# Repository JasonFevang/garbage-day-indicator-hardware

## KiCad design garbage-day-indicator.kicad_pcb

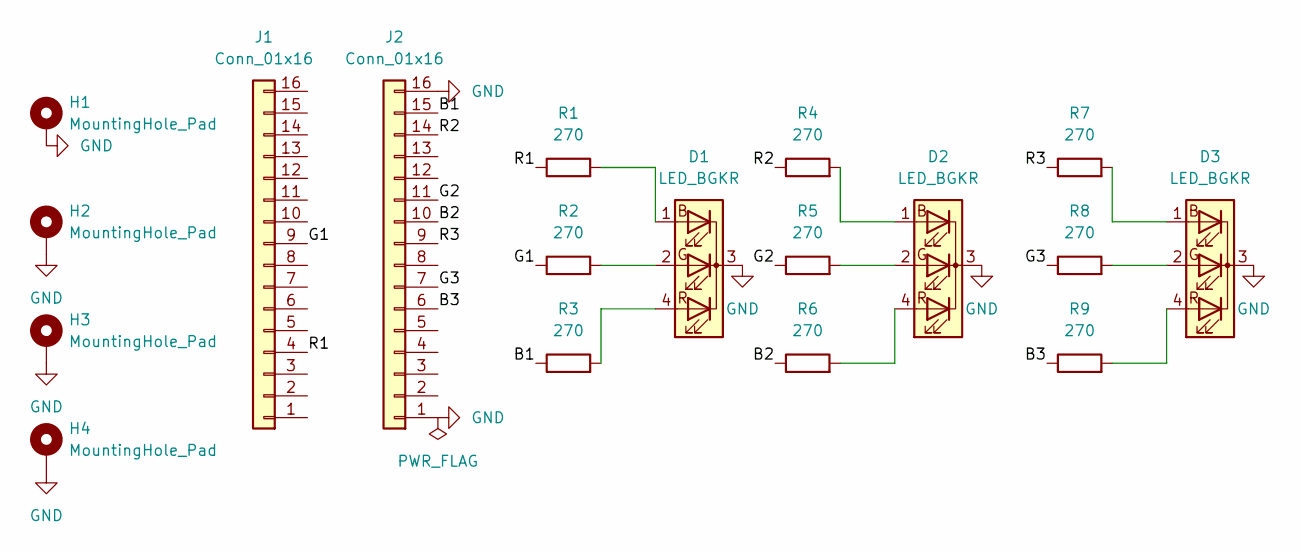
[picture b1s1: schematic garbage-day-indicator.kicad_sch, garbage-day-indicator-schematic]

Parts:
D1, D2, D3: LED_BGKR; LED_D5.0mm-4_RGB
H1, H2, H3, H4: MountingHole_Pad; MountingHole_3.2mm_M3_DIN965_Pad
J1, J2: Conn_01x16; PinSocket_1x16_P2.54mm_Vertical
R1, R2, R3, R4, R5, R6, R7, R8, R9: 270; R_0603_1608Metric

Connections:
/B1: J2.15, R3.1
/B2: J2.10, R6.1
/B3: J2.6, R9.1
/G1: J1.9, R2.1
/G2: J2.11, R5.1
/G3: J2.7, R8.1
/R1: J1.4, R1.1
/R2: J2.14, R4.1
/R3: J2.9, R7.1
GND: D1.3 (K), D2.3 (K), D3.3 (K), H1.1, H2.1, H3.1, H4.1, J2.1, J2.16
unnamed: D1.1 (BA), R1.2
unnamed: D1.2 (GA), R2.2
unnamed: D1.4 (RA), R3.2
unnamed: D2.1 (BA), R4.2
unnamed: D2.2 (GA), R5.2
unnamed: D2.4 (RA), R6.2
unnamed: D3.1 (BA), R7.2
unnamed: D3.2 (GA), R8.2
unnamed: D3.4 (RA), R9.2

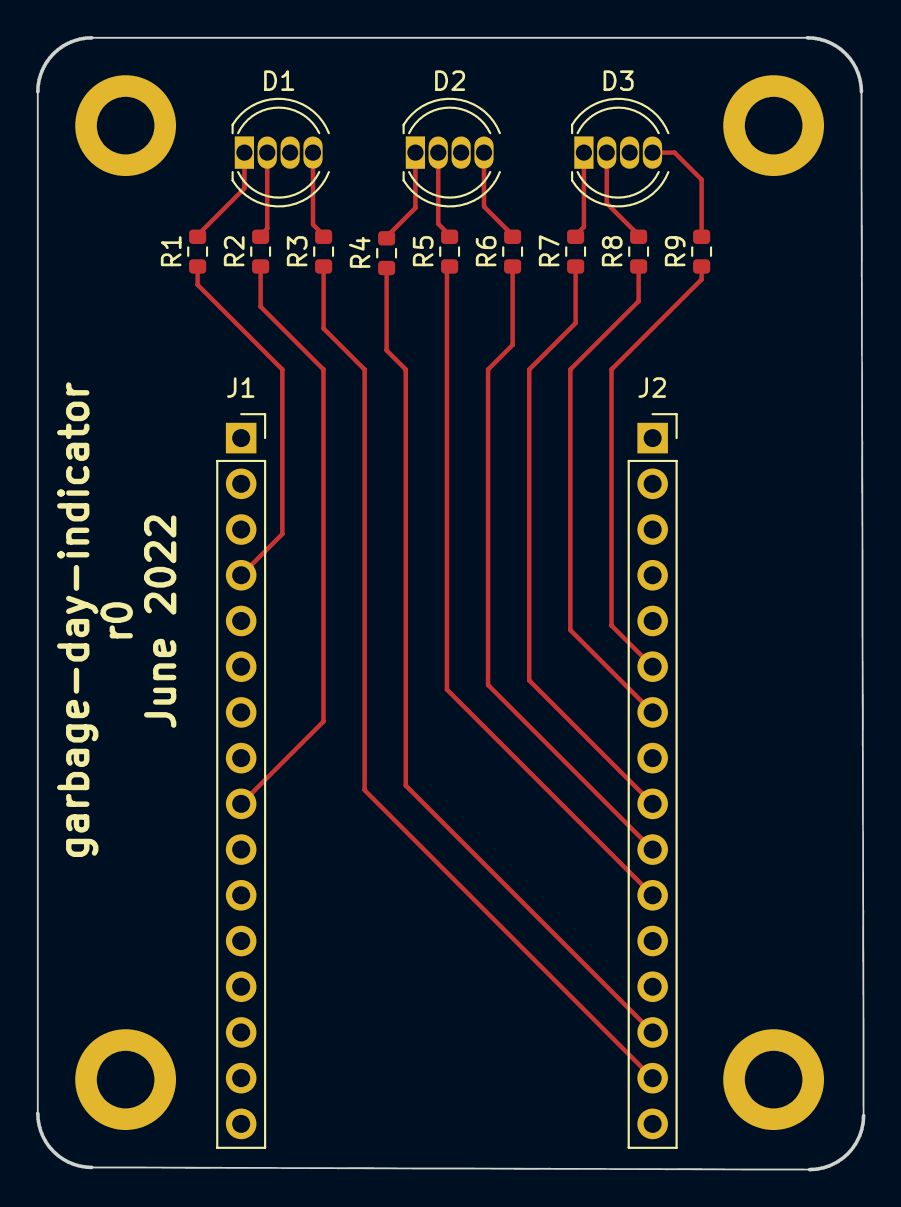
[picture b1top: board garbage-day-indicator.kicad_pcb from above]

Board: 2 copper layers, 45.9 x 62.9 mm, 18 parts (0 on the bottom side), 19 nets.

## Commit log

2022-06-16 Improve pcb layout
2022-06-20 Improved traces, added silkscreen revision/name
